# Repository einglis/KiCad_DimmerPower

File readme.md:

# Dimmer Power Board

A power board for my lounge dimmer project.  Ultimately driven by an Arduino running code in https://github.com/einglis/dimmer.  (And a RaspberyPI providing a UI, and another Arduino receiving Rako wireless commands, both also running code from the same repo.)

Originally based on https://www.instructables.com/Multichannel-Wireless-Light-Dimmer/

At the time of writing, the six live boards have got 5 years of successful operation under their belts.

## Version History
I drew this originally in Eagle, but the committed project is for KiCad.  KiCad seemed to import it just fine and the schematic and board layout look identical to the production parts; the gerbers in the `output/` folder check out too.

All the same, I preserved the bulk of the Eagle files in the `retired/` folder, just in case.  They show signs of sequential-numbering version control...

## Pictures

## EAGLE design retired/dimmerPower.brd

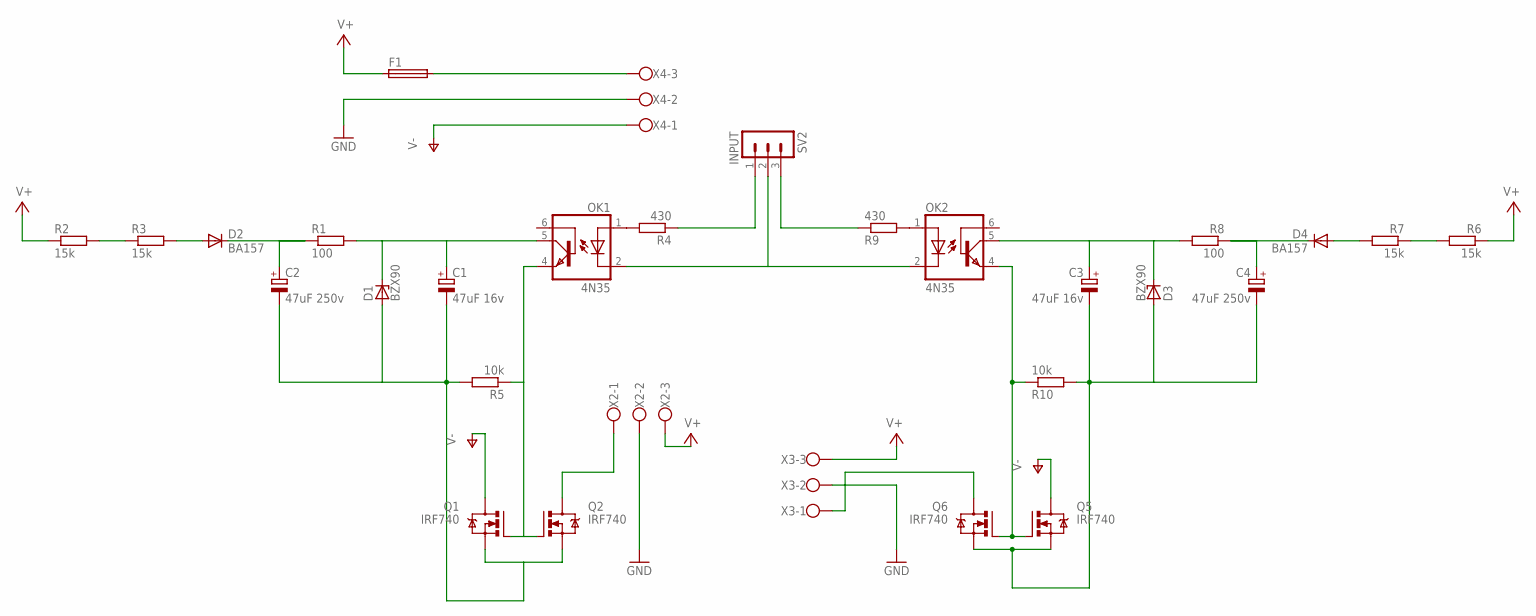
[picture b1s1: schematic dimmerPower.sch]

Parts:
C1, C3: 47uF 16v; E2,5-6
C2, C4: 47uF 250v; E5-13
D1, D3: BZX90; DO34Z7
D2, D4: BA157; P1-10
F1: SH22,5
OK1, OK2: 4N35; DIL06
Q1, Q2, Q5, Q6: IRF740; TO220BV
R1, R8: 100; 0204/7
R2, R3, R6, R7: 15k; P0613/15
R4, R9: 430; 0204/7
R5, R10: 10k; 0204/7
SV2: INPUT; MA03-1
X2, X3, X4: W237-103

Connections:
GND: X2.2, X3.2, X4.2
unnamed: Q6.D, X3.1
unnamed: OK1.2 (C), OK2.2 (C), SV2.2
unnamed: OK1.1 (A), R4.2
unnamed: C3.-, C4.-, D3.A, Q5.S, Q6.S, R10.2
unnamed: C1.-, C2.-, D1.A, Q1.S, Q2.S, R5.2
unnamed: R2.2, R3.1
unnamed: D2.A, R3.2
unnamed: C2.+, D2.C, R1.1
unnamed: C1.+, D1.C, OK1.5 (COL), R1.2
unnamed: R4.1, SV2.1
unnamed: Q2.D, X2.1
unnamed: R6.2, R7.1
unnamed: D4.A, R7.2
unnamed: C4.+, D4.C, R8.1
unnamed: C3.+, D3.C, OK2.5 (COL), R8.2
unnamed: R9.1, SV2.3
unnamed: OK2.1 (A), R9.2
unnamed: OK1.4 (EMI), Q1.G, Q2.G, R5.1
unnamed: OK2.4 (EMI), Q5.G, Q6.G, R10.1
V+: F1.1, R2.1, R6.1, X2.3, X3.3
V+1: F1.2, X4.3
V-: Q1.D, Q5.D, X4.1

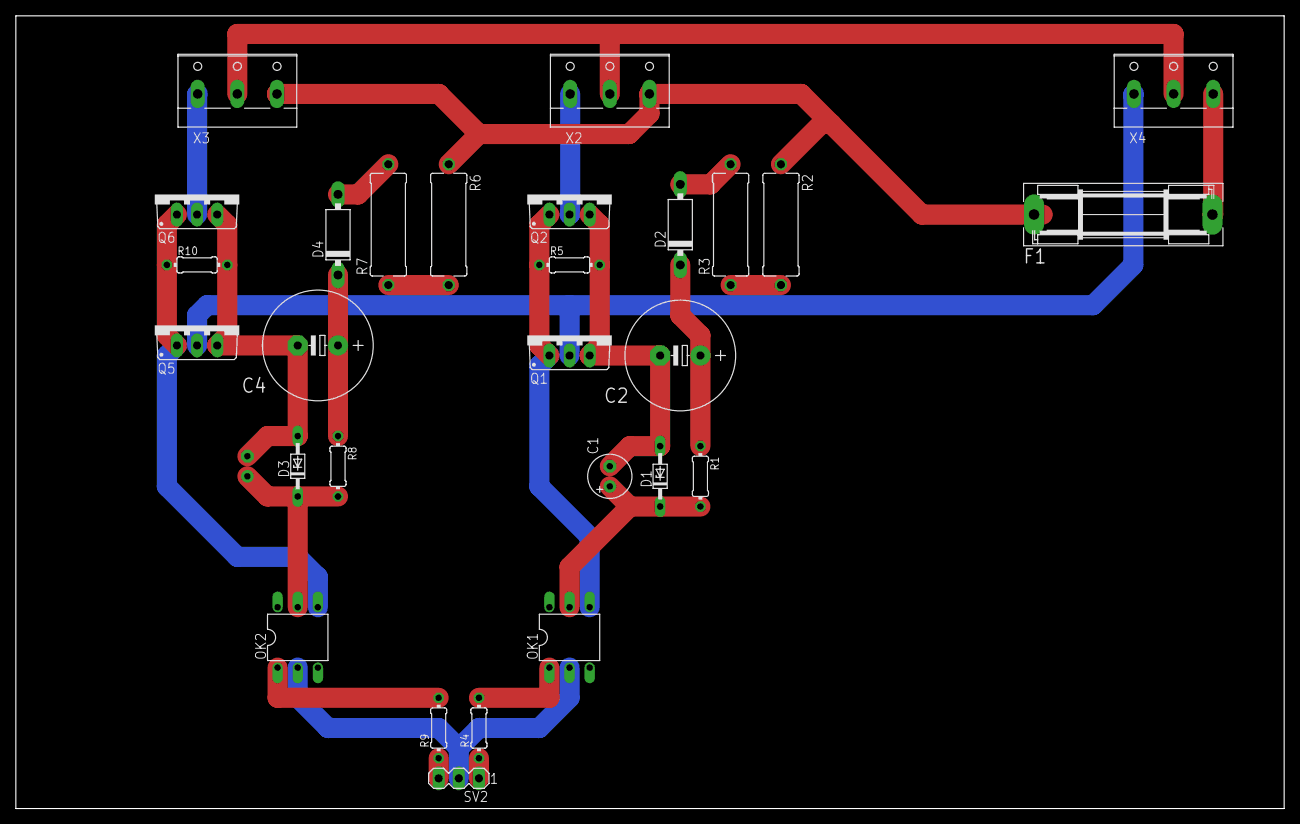
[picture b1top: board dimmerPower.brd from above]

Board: 2 copper layers, 160.0 x 100.0 mm, 29 parts (1 on the bottom side), 23 nets.

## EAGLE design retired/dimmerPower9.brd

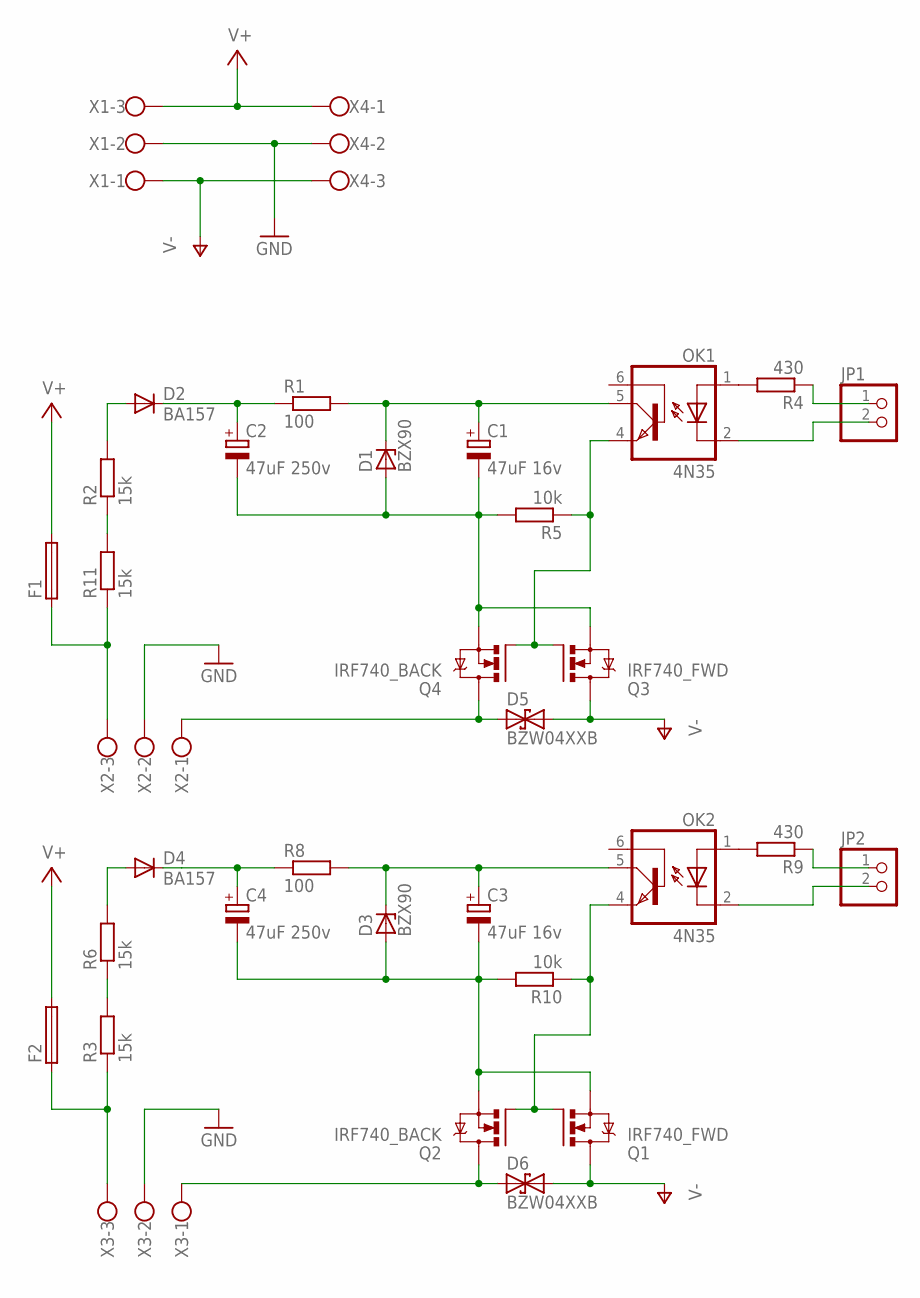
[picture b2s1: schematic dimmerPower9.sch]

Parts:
C1, C3: 47uF 16v; E2,5-6
C2, C4: 47uF 250v; E5-13
D1, D3: BZX90; DO34Z7
D2, D4: BA157; P1-10
D5, D6: BZW04XXB; F126Z12
F1, F2: SH22,5
JP1, JP2: PINHD-1X2; 1X02
OK1, OK2: 4N35; DIL06
Q1, Q3: IRF740_FWD; TO220BV_FWD
Q2, Q4: IRF740_BACK; TO220BV_BACK
R1, R8: 100; 0204/7
R2, R3, R6, R11: 15k; P0613/15
R4, R9: 430; 0204/7
R5, R10: 10k; 0204/7
X1, X2, X3, X4: W237-103

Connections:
GND: X1.2, X2.2, X3.2, X4.2
unnamed: C1.-, C2.-, D1.A, Q3.S, Q4.S, R5.2
unnamed: JP1.1, R4.1
unnamed: OK1.1 (A), R4.2
unnamed: JP1.2, OK1.2 (C)
unnamed: F1.1, R11.1, X2.3
unnamed: R3.2, R6.1
unnamed: R2.1, R11.2
unnamed: D2.A, R2.2
unnamed: C2.+, D2.C, R1.1
unnamed: C1.+, D1.C, OK1.5 (COL), R1.2
unnamed: OK1.4 (EMI), Q3.G, Q4.G, R5.1
unnamed: D5.A (1), Q4.D, X2.1
unnamed: D4.A, R6.2
unnamed: C4.+, D4.C, R8.1
unnamed: C3.+, D3.C, OK2.5 (COL), R8.2
unnamed: OK2.1 (A), R9.2
unnamed: D6.A (1), Q2.D, X3.1
unnamed: JP2.1, R9.1
unnamed: JP2.2, OK2.2 (C)
unnamed: OK2.4 (EMI), Q1.G, Q2.G, R10.1
unnamed: C3.-, C4.-, D3.A, Q1.S, Q2.S, R10.2
unnamed: F2.1, R3.1, X3.3
V+: F1.2, F2.2, X1.3, X4.1
V-: D5.C (2), D6.C (2), Q1.D, Q3.D, X1.1, X4.3

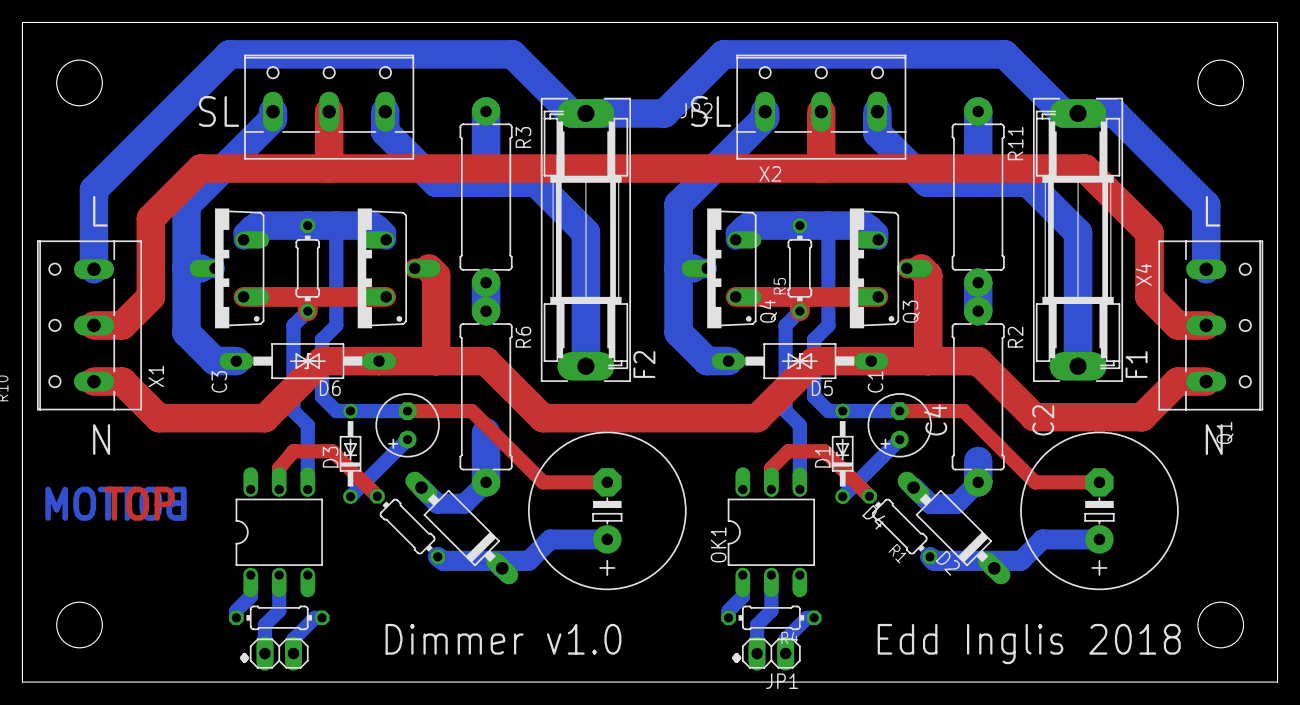
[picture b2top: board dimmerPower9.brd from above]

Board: 2 copper layers, 111.7 x 58.7 mm, 34 parts (0 on the bottom side), 25 nets.

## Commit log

2023-12-16 adding gerbers
2023-12-16 This was originally drawn with Eagle; out of paranoia, I'm committing all the files I have from that era, though the main KiCad project looks exactly like that which was produced
2023-12-16 docs
2023-12-16 pictures
